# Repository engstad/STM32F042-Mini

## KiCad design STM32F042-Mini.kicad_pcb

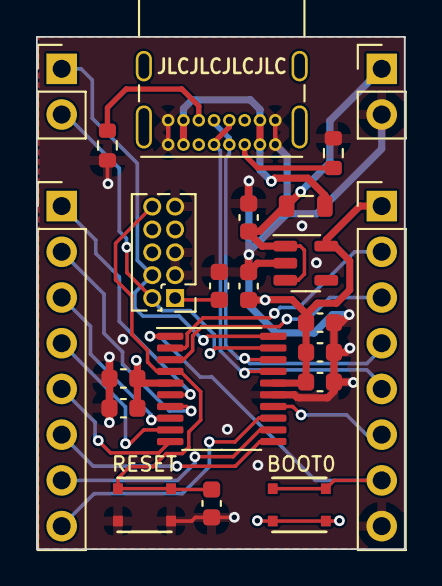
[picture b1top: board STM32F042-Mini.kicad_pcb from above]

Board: 4 copper layers, 20.4 x 28.5 mm, 22 parts (0 on the bottom side), 23 nets.

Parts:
C1: 4u7; C_0603_1608Metric
C2, C3, C6, C7: 100n; C_0603_1608Metric
C4, C9, C10: 1u; C_0603_1608Metric
C5: 10n; C_0603_1608Metric
FB1: FerriteBead_Small; L_0805_2012Metric
J1: LPINS; PinHeader_1x08_P2.54mm_Vertical
J2: RPINS; PinHeader_1x08_P2.54mm_Vertical
J3: BUS_PWR; PinHeader_1x02_P2.54mm_Vertical
J4: USB_C_Receptacle_USB2.0; USB_C_Receptacle_GCT_USB4085
J5: SWD; PinHeader_1x02_P2.54mm_Vertical
P1: CORTEX-JTAG; PinHeader_2x05_P1.27mm_Vertical
R1, R2: 5K1; R_0603_1608Metric
SW1: RST; tactile-switch-evpay-34x29mm
SW2: BOOT0; tactile-switch-evpay-34x29mm
U1: STM32F042F6Px; TSSOP-20_4.4x6.5mm_P0.65mm
U2: TLV75733PDBVR‎; SOT-23-5

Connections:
+3V3: C1.1, C2.1, C3.1, C4.1, C5.1, C7.1, C10.1, J2.1, P1.1, SW2.1, U1.5 (VDDA), U1.16 (VDD), U2.5 (OUT)
/CC1: J4.A5 (CC1), R2.1
/CC2: J4.B5 (CC2), R1.1
/PA0: J1.1, U1.6 (PA0)
/PA1: J1.2, U1.7 (PA1)
/PA2: J1.3, U1.8 (PA2)
/PA3: J1.4, U1.9 (PA3)
/PA4: J1.5, U1.10 (PA4)
/PA5: J1.6, U1.11 (PA5)
/PA6: J1.7, U1.12 (PA6)
/PA7: J1.8, U1.13 (PA7)
/PB1: J2.6, U1.14 (PB1)
/PB8: J2.7, SW2.2, U1.1 (PB8)
/PF0: J2.2, U1.2 (PF0)
/PF1: J2.3, U1.3 (PF1)
/SWCLK: J5.1, P1.4, U1.20 (PA14)
/SWDIO: J5.2, P1.2, U1.19 (PA13)
/USB_D+: J2.4, J4.A6 (D+), J4.B6 (D+), U1.18 (PA10/PA12)
/USB_D-: J2.5, J4.A7 (D-), J4.B7 (D-), U1.17 (PA9/PA11)
/USB_VBUS: FB1.1, J4.A4 (VBUS), J4.A9 (VBUS), J4.B4 (VBUS), J4.B9 (VBUS)
/~RST: C6.1, P1.10, SW1.2, U1.4 (NRST)
GND: C1.2, C2.2, C3.2, C4.2, C5.2, C6.2, C7.2, C9.2, C10.2, J2.8, J3.2, J4.A1 (GND), J4.A12 (GND), J4.B1 (GND), J4.B12 (GND), P1.3, P1.5, P1.9, R1.2, R2.2, SW1.1, U1.15 (VSSA), U2.2 (GND)
VBUS: C9.1, FB1.2, J3.1, U2.1 (IN), U2.3 (EN)

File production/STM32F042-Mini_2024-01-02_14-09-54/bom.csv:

Designator,Footprint,Quantity,Value,LCSC Part #
C1,0603,1,4u7,
"C10, C4, C9",0603,3,1u,
"C2, C3, C6, C7",0603,4,100n,
C5,0603,1,10n,
FB1,0805,1,FerriteBead_Small,
J1,PinHeader_1x08_P2.54mm_Vertical,1,LPINS,
J2,PinHeader_1x08_P2.54mm_Vertical,1,RPINS,
J3,PinHeader_1x02_P2.54mm_Vertical,1,BUS_PWR,
J4,USB_C_Receptacle_GCT_USB4085,1,USB_C_Receptacle_USB2.0,
J5,PinHeader_1x02_P2.54mm_Vertical,1,SWD,
P1,PinHeader_2x05_P1.27mm_Vertical,1,CORTEX-JTAG,
"R1, R2",0603,2,5K1,
SW1,tactile-switch-evpay-34x29mm,1,RST,
SW2,tactile-switch-evpay-34x29mm,1,BOOT0,
U1,TSSOP-20_4.4x6.5mm_P0.65mm,1,STM32F042F6Px,
U2,SOT-23-5,1,TLV75733PDBVR‎,

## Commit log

2024-01-12 Initial commit.
